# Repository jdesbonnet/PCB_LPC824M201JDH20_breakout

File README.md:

# PCB_LPC824M201JDH20_breakout

Breakout board for TSSOP package version of LPC824 ARM Cortex-M0+ MCU. 

Features:

 * Extra long IC pin leads which makes handsoldering easier.
 * Option for crystal + 2C mounted underside. Crystal component height needs to be 2mm or less.
 * Option for one or two bypass 0602 capacitors (right above the IC).
 * Option for 0602 LED + R on PIO0_23 (package pin 1).

## History

Version 0.8.1, 2018-05-12

Changes to silk screen layer to make purpose of passive components clearer. 
Add link to project git repo.

Version 0.8.0, 2018-04-24

Sent to OSHPark.com for fabrication. PCB arrived 2018-05-11. Works as expected. Only thing I'd change is 
marking the optional bypass and LED pads more clearly. I haven't tested the crystal.

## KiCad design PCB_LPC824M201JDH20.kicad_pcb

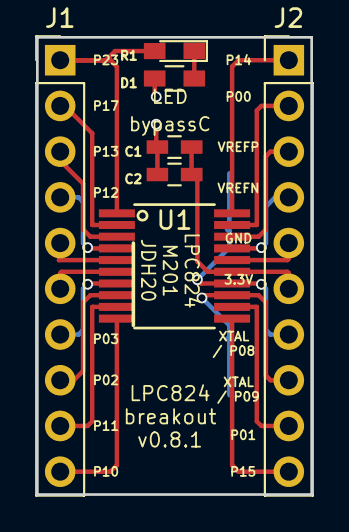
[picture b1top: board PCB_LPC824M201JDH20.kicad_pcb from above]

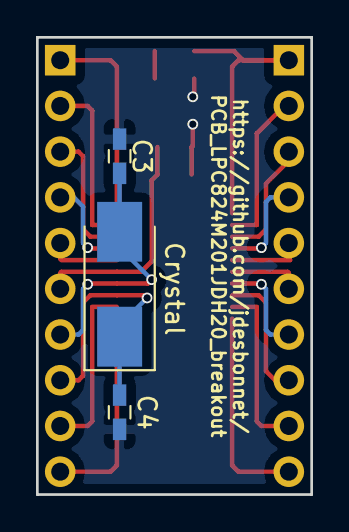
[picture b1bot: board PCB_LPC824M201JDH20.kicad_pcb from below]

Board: 2 copper layers, 15.2 x 25.4 mm, 10 parts (3 on the bottom side), 21 nets.

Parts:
C1, C2, C3, C4: C; C_0603_HandSoldering
Crystal: Crystal; Crystal_SMD_0603-2pin_6.0x3.5mm_HandSoldering
D1: LED; LED_0603_HandSoldering
J1, J2: Conn_01x10; Pin_Header_Straight_1x10_Pitch2.54mm
R1: R; R_0603_HandSoldering
U1: LPC824M201JDH20; TSSOP-20_4.4x6.5mm_Pitch0.65mm

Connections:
3.3V: C1.1, C2.1, J2.6, U1.15
GND: C1.2, C2.2, C3.1, C4.1, J2.5, R1.1, U1.16
LED: D1.2, J1.1, U1.1
unnamed: D1.1, R1.2
PIO0_0: J2.2, U1.19
PIO0_1: J2.9, U1.12
PIO0_2: J1.8, U1.8
PIO0_3: J1.7, U1.7
PIO0_4: J1.6, U1.6
PIO0_5: J1.5, U1.5
PIO0_10: J1.10, U1.10
PIO0_11: J1.9, U1.9
PIO0_12: J1.4, U1.4
PIO0_13: J1.3, U1.3
PIO0_14: J2.1, U1.20
PIO0_15: J2.10, U1.11
PIO0_17: J1.2, U1.2
VREFN: J2.4, U1.17
VREFP: J2.3, U1.18
XTALIN: C3.2, Crystal.2, J2.7, U1.14
XTALOUT: C4.2, Crystal.1, J2.8, U1.13

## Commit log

2018-04-22 no comment
2018-04-22 add README.md
2018-05-12 ground pour
2018-05-12 fix front silkscreen
2018-05-12 fix back silkscreen, add URL to github repo
2018-05-12 add 3D renders to readme
2018-05-12 add photo
2018-05-12 fix markdown typo
